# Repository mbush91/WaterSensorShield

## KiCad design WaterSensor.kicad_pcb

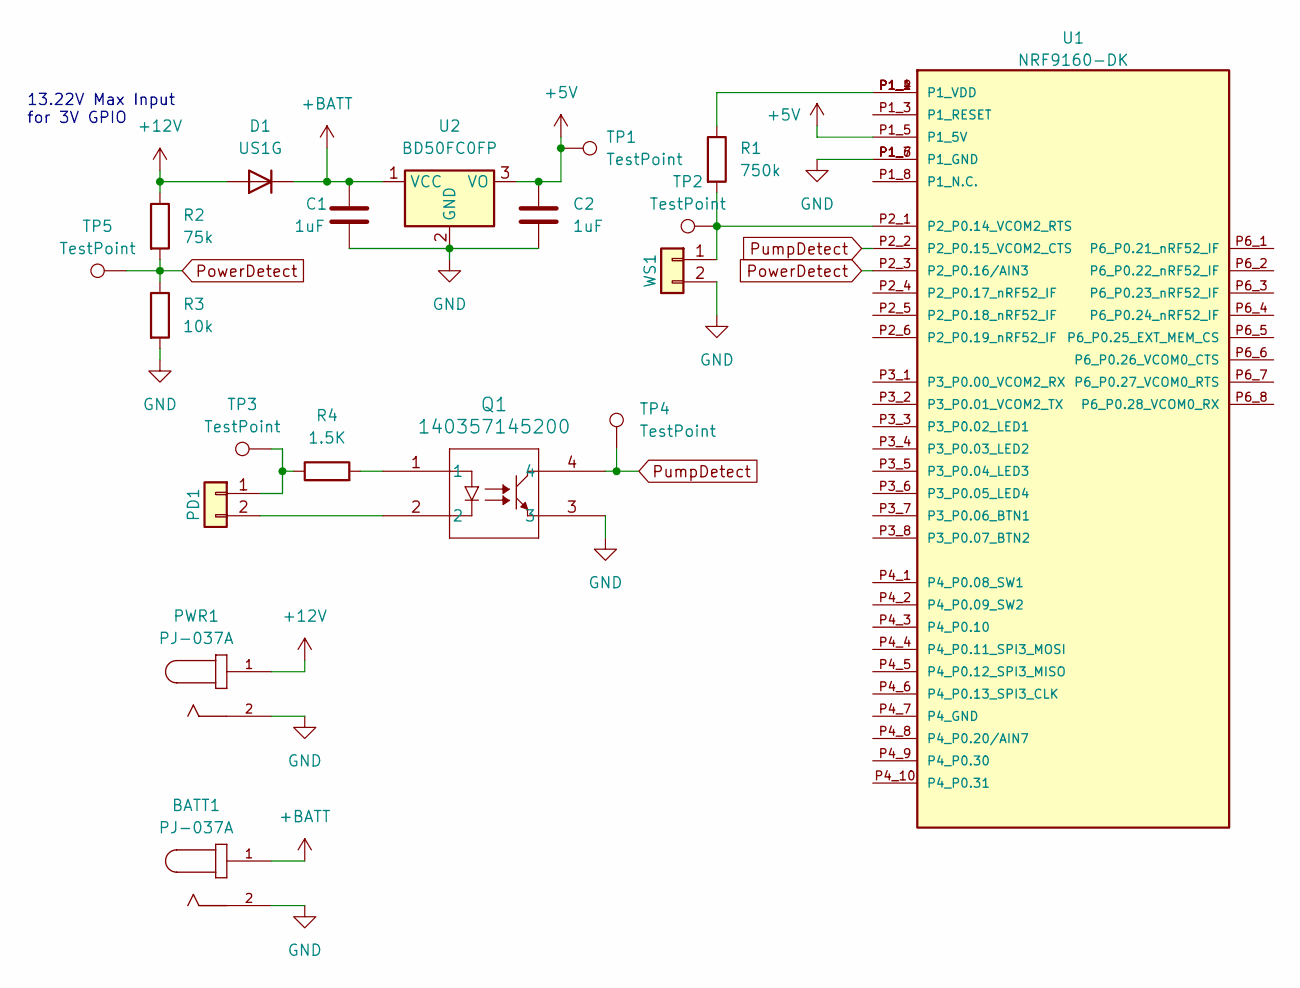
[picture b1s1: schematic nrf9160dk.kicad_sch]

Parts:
BATT1: PJ-037A; CUI_PJ-037A
C1, C2: 1uF; C_0603_1608Metric_Pad1.08x0.95mm_HandSolder
D1: US1G; D_SMA
PD1: Conn_01x02; PinHeader_1x02_P2.54mm_Vertical
PWR1: PJ-037A; CUI_PJ-037A
Q1: 140357145200; WL-OCPT_SOP4_WRE
R1: 750k; R_0805_2012Metric_Pad1.20x1.40mm_HandSolder
R2: 75k; R_0805_2012Metric_Pad1.20x1.40mm_HandSolder
R3: 10k; R_0805_2012Metric_Pad1.20x1.40mm_HandSolder
R4: 1.5K; R_0805_2012Metric_Pad1.20x1.40mm_HandSolder
TP1, TP2, TP3, TP4, TP5: TestPoint; TestPoint_Pad_D1.0mm
U1: NRF9160-DK; MODULE_NRF9160-DK; MPN NRF9160-DK
U2: BD50FC0FP; TO-252-2
WS1: Conn_01x02; PinHeader_1x02_P2.54mm_Vertical

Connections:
+5V: C2.1, TP1.1, U1.P1_5 (P1_5V), U2.3 (VO)
+12V: D1.2 (A), PWR1.1, R2.1
+BATT: BATT1.1, C1.1, D1.1 (K), U2.1 (VCC)
GND: BATT1.2, C1.2, C2.2, PWR1.2, Q1.3, R3.2, U1.P1_6 (P1_GND), U1.P1_7 (P1_GND), U2.2 (GND), WS1.2
unnamed: PD1.1, R4.1, TP3.1
unnamed: PD1.2, Q1.2
unnamed: Q1.1, R4.2
unnamed: R1.1, U1.P1_1 (P1_VDD), U1.P1_2 (P1_VDD), U1.P1_4 (P1_VDD)
unnamed: R1.2, TP2.1, U1.P2_1 (P2_P0.14_VCOM2_RTS), WS1.1
PowerDetect: R2.2, R3.1, TP5.1, U1.P2_3 (P2_P0.16/AIN3)
PumpDetect: Q1.4, TP4.1, U1.P2_2 (P2_P0.15_VCOM2_CTS)

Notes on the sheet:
13.22V Max Input for 3V GPIO

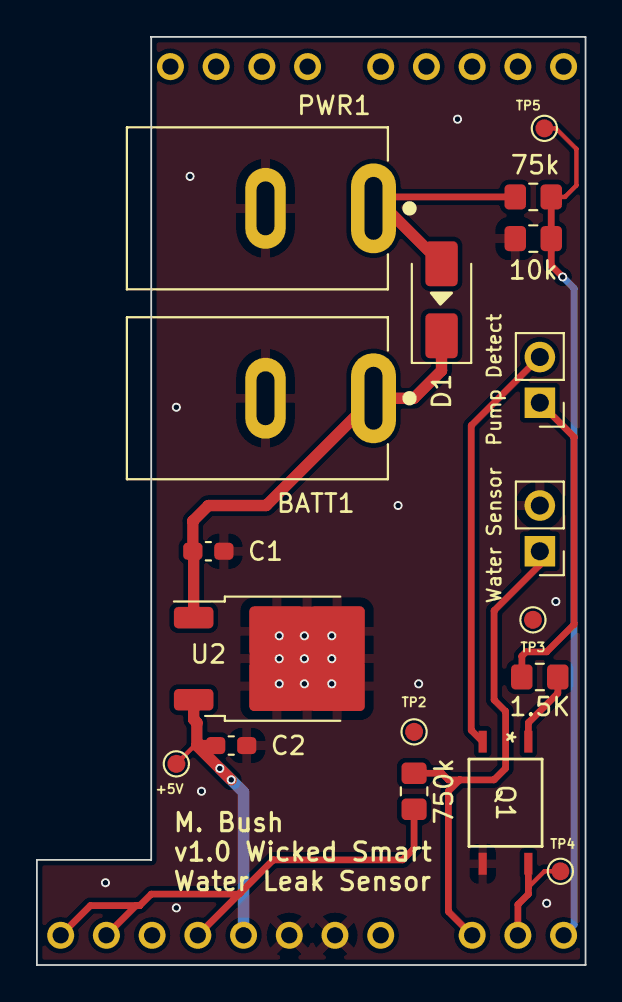
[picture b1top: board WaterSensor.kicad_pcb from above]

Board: 2 copper layers, 30.5 x 51.6 mm, 19 parts (0 on the bottom side), 11 nets.

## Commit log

2024-04-10 inital commit
2024-04-11 add libs
2024-04-11 board v1.0
2024-05-02 update to prod stuff
2024-05-02 moved to subfolder
2024-05-02 rename
2024-05-05 android app template
2024-05-05 fix weird submodule
2024-05-05 add back zephyr
